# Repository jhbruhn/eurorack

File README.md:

# eurorack modules

Welcome to my Eurorack module stash. This is a collection of modules I (partially) designed for use with eurorack synthesizers.

## modules

* **bus**: A tiny bus. not much to say.
* **out**: Befaco Outs on a separate pcb with SMD parts to manufacture it via JLC
* **pure_adsr**: Alternative firmware for the old GMSN Pure ADSR modules, using ADSR and mini sequencer modes from Peaks and a weird looping ADSR thing on mode 3
* **stereo_mix**: a 4 channel stereo (input AND output) mixer with voltage-controlled panning and volume. Digitally controlled via Multiplying DACs (MCP4922 in combination with MCP4822)
* **vca**: A dual channel variable slope (exp/lin/log) VCA based on easily available components
* **vcf-20**: MS20 style filter
* **vcf-leiter**: Moog style filter

## license

Code: MIT license.

Hardware: cc-by-sa-3.0

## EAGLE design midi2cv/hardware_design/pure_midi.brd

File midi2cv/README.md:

# midi2cv
Eurorack Compatible, Arduino-based midi to cv converter with mono mode, arpeggiator and sequencer

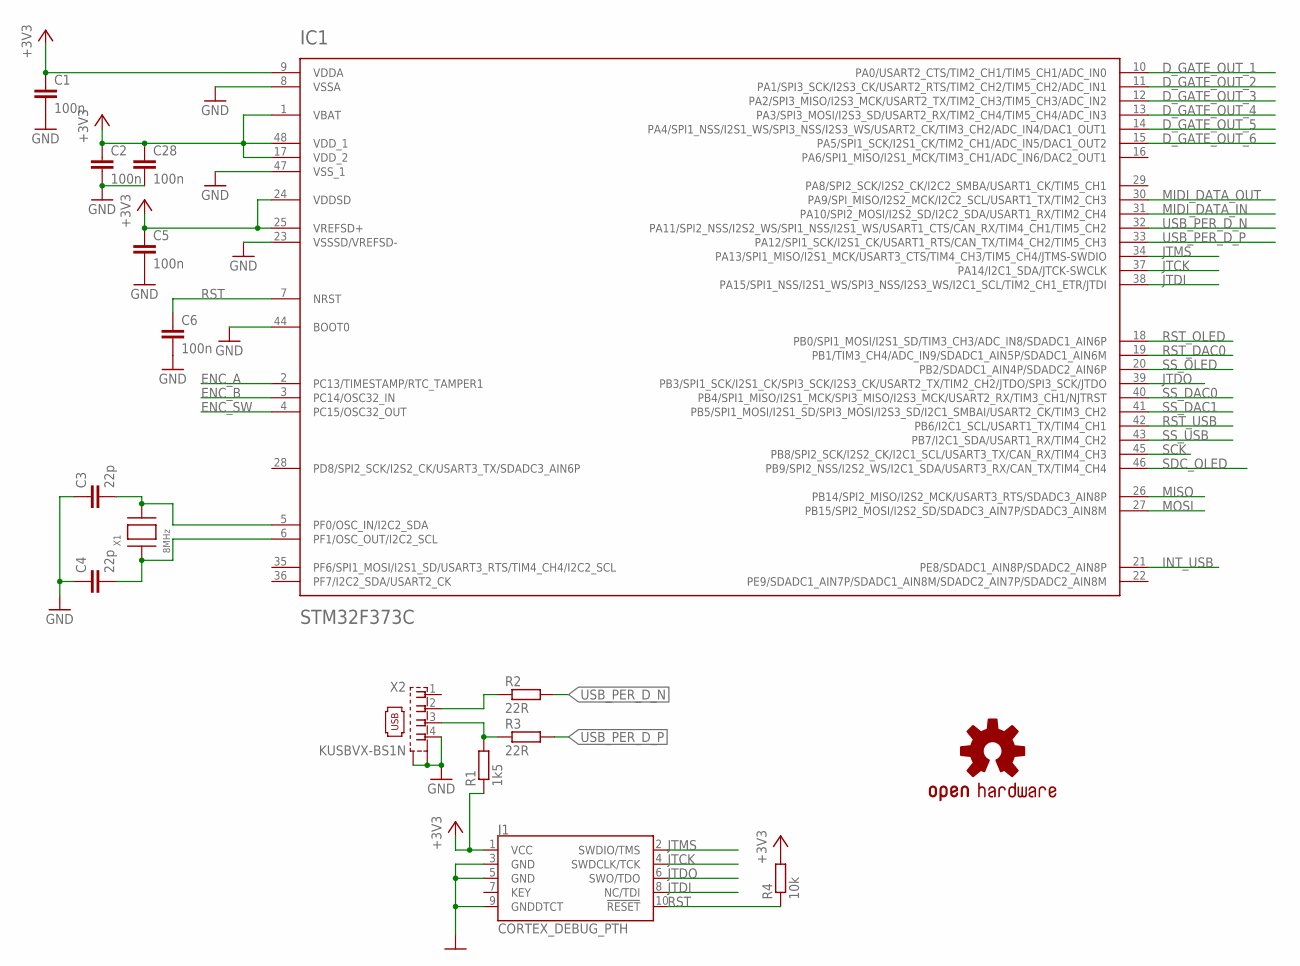
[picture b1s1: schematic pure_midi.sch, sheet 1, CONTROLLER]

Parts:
C1, C2, C5, C6, C28: 100n; C0603
C3, C4: 22p; C0603
IC1: STM32F373C; LQFP48
J1: CORTEX_DEBUG_PTH; 2X5-PTH-1.27MM
LOGO1: OSHW-LOGOM; OSHW-LOGO-M
R1: 1k5; R0603
R2, R3: 22R; R0603
R4: 10k; R0603
X1: 8MHz; NX5032
X2: KUSBVX-BS1N

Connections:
+3V3: C1.1, C2.1, C5.1, C28.1, IC1.1 (VBAT), IC1.9 (VDDA), IC1.17 (VDD_2), IC1.24 (VDDSD), IC1.25 (VREFSD+), IC1.48 (VDD_1), J1.1 (VCC), R1.1, R4.2; also elsewhere on the board
D_GATE_OUT_1: IC1.10 (PA0/USART2_CTS/TIM2_CH1/TIM5_CH1/ADC_IN0); also elsewhere on the board
D_GATE_OUT_2: IC1.11 (PA1/SPI3_SCK/I2S3_CK/USART2_RTS/TIM2_CH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); also elsewhere on the board
D_GATE_OUT_3: IC1.12 (PA2/SPI3_MISO/I2S3_MCK/USART2_TX/TIM2_C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); also elsewhere on the board
D_GATE_OUT_4: IC1.13 (PA3/SPI3_MOSI/I2S3_SD/USART2_RX/TIM2_CH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); also elsewhere on the board
D_GATE_OUT_5: IC1.14 (PA4/SPI1_NSS/I2S1_WS/SPI3_NSS/I2S3_WS/U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); also elsewhere on the board
D_GATE_OUT_6: IC1.15 (PA5/SPI1_SCK/I2S1_CK/TIM2_CH1/ADC_IN5/D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); also elsewhere on the board
ENC_A: IC1.2 (PC13/TIMESTAMP/RTC_TAMPER1); also elsewhere on the board
ENC_B: IC1.3 (PC14/OSC32_IN); also elsewhere on the board
ENC_SW: IC1.4 (PC15/OSC32_OUT); also elsewhere on the board
GND: C1.2, C2.2, C3.1, C4.1, C5.2, C6.2, C28.2, IC1.8 (VSSA), IC1.23 (VSSSD/VREFSD-), IC1.44 (BOOT0), IC1.47 (VSS_1), J1.3 (GND), J1.5 (GND), J1.9 (GNDDTCT), X2.4, X2.M1 (S1), X2.M2 (S2); also elsewhere on the board
INT_USB: IC1.21 (PE8/SDADC1_AIN8P/SDADC2_AIN8P)
JTCK: IC1.37 (PA14/I2C1_SDA/JTCK-SWCLK), J1.4 (SWDCLK/TCK)
JTDI: IC1.38 (PA15/SPI1_NSS/I2S1_WS/SPI3_NSS/I2S3_WS/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), J1.8 (NC/TDI)
JTDO: IC1.39 (PB3/SPI1_SCK/I2S1_CK/SPI3_SCK/I2S3_CK/U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), J1.6 (SWO/TDO)
JTMS: IC1.34 (PA13/SPI1_MISO/I2S1_MCK/USART3_CTS/TIM4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), J1.2 (SWDIO/TMS)
MIDI_DATA_IN: IC1.31 (PA10/SPI2_MOSI/I2S2_SD/I2C2_SDA/USART1_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); also elsewhere on the board
MIDI_DATA_OUT: IC1.30 (PA9/SPI_MISO/I2S2_MCK/I2C2_SCL/USART1_T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); also elsewhere on the board
MISO: IC1.26 (PB14/SPI2_MISO/I2S2_MCK/USART3_RTS/SDAD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)
MOSI: IC1.27 (PB15/SPI2_MOSI/I2S2_SD/SDADC3_AIN7P/SDA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); also elsewhere on the board
unnamed: C4.2, IC1.6 (PF1/OSC_OUT/I2C2_SCL), X1.P$1
unnamed: C3.2, IC1.5 (PF0/OSC_IN/I2C2_SDA), X1.P$2
unnamed: R2.1, X2.2
unnamed: R1.2, R3.1, X2.3
RST: C6.1, IC1.7 (NRST), J1.10 (!RESET), R4.1
RST_DAC0: IC1.19 (PB1/TIM3_CH4/ADC_IN9/SDADC1_AIN5P/SDADC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); also elsewhere on the board
RST_OLED: IC1.18 (PB0/SPI1_MOSI/I2S1_SD/TIM3_CH3/ADC_IN8/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); also elsewhere on the board
RST_USB: IC1.42 (PB6/I2C1_SCL/USART1_TX/TIM4_CH1)
SCK: IC1.45 (PB8/SPI2_SCK/I2S2_CK/I2C1_SCL/USART3_TX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); also elsewhere on the board
SDC_OLED: IC1.46 (PB9/SPI2_NSS/I2S2_WS/I2C1_SDA/USART3_RX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); also elsewhere on the board
SS_DAC0: IC1.40 (PB4/SPI1_MISO/I2S1_MCK/SPI3_MISO/I2S3_M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); also elsewhere on the board
SS_DAC1: IC1.41 (PB5/SPI1_MOSI/I2S1_SD/SPI3_MOSI/I2S3_SD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); also elsewhere on the board
SS_OLED: IC1.20 (PB2/SDADC1_AIN4P/SDADC2_AIN6P); also elsewhere on the board
SS_USB: IC1.43 (PB7/I2C1_SDA/USART1_RX/TIM4_CH2)
USB_PER_D_N: IC1.32 (PA11/SPI2_NSS/I2S2_WS/SPI1_NSS/I2S1_WS/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), R2.2
USB_PER_D_P: IC1.33 (PA12/SPI1_SCK/I2S1_CK/USART1_RTS/CAN_TX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), R3.2

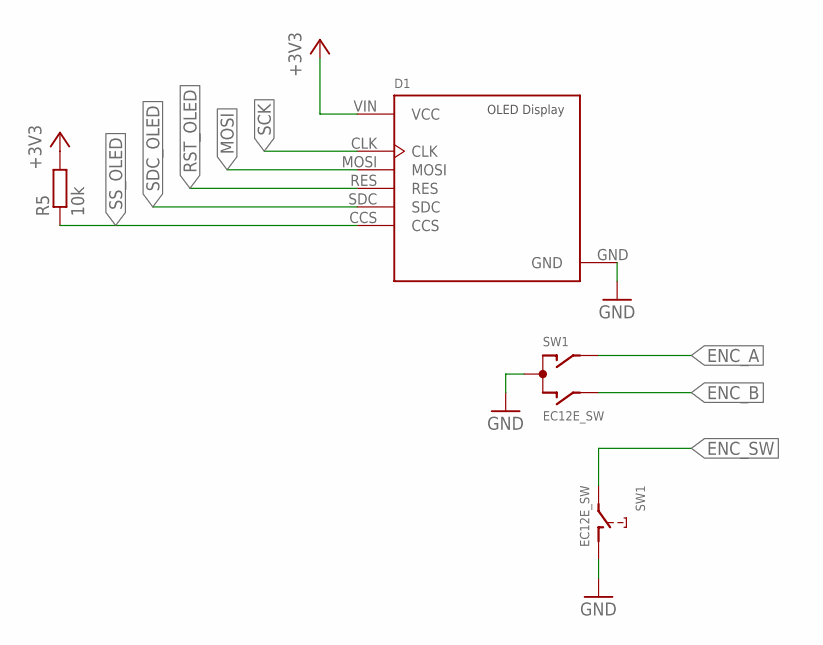
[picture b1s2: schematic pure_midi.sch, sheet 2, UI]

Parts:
D1: OLED_1.3_128X64_SPI; C1_ADAFRUIT_1.3_128X64_OLED
R5: 10k; R0603
SW1: EC12E_SW; ALPS_EC12E_SW

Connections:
+3V3: D1.VIN (VCC), R5.2; also elsewhere on the board
ENC_A: SW1.A; also elsewhere on the board
ENC_B: SW1.B; also elsewhere on the board
ENC_SW: SW1.E (2); also elsewhere on the board
GND: D1.GND, SW1.C, SW1.D (1); also elsewhere on the board
MOSI: D1.MOSI; also elsewhere on the board
RST_OLED: D1.RES; also elsewhere on the board
SCK: D1.CLK; also elsewhere on the board
SDC_OLED: D1.SDC; also elsewhere on the board
SS_OLED: D1.CCS, R5.1; also elsewhere on the board

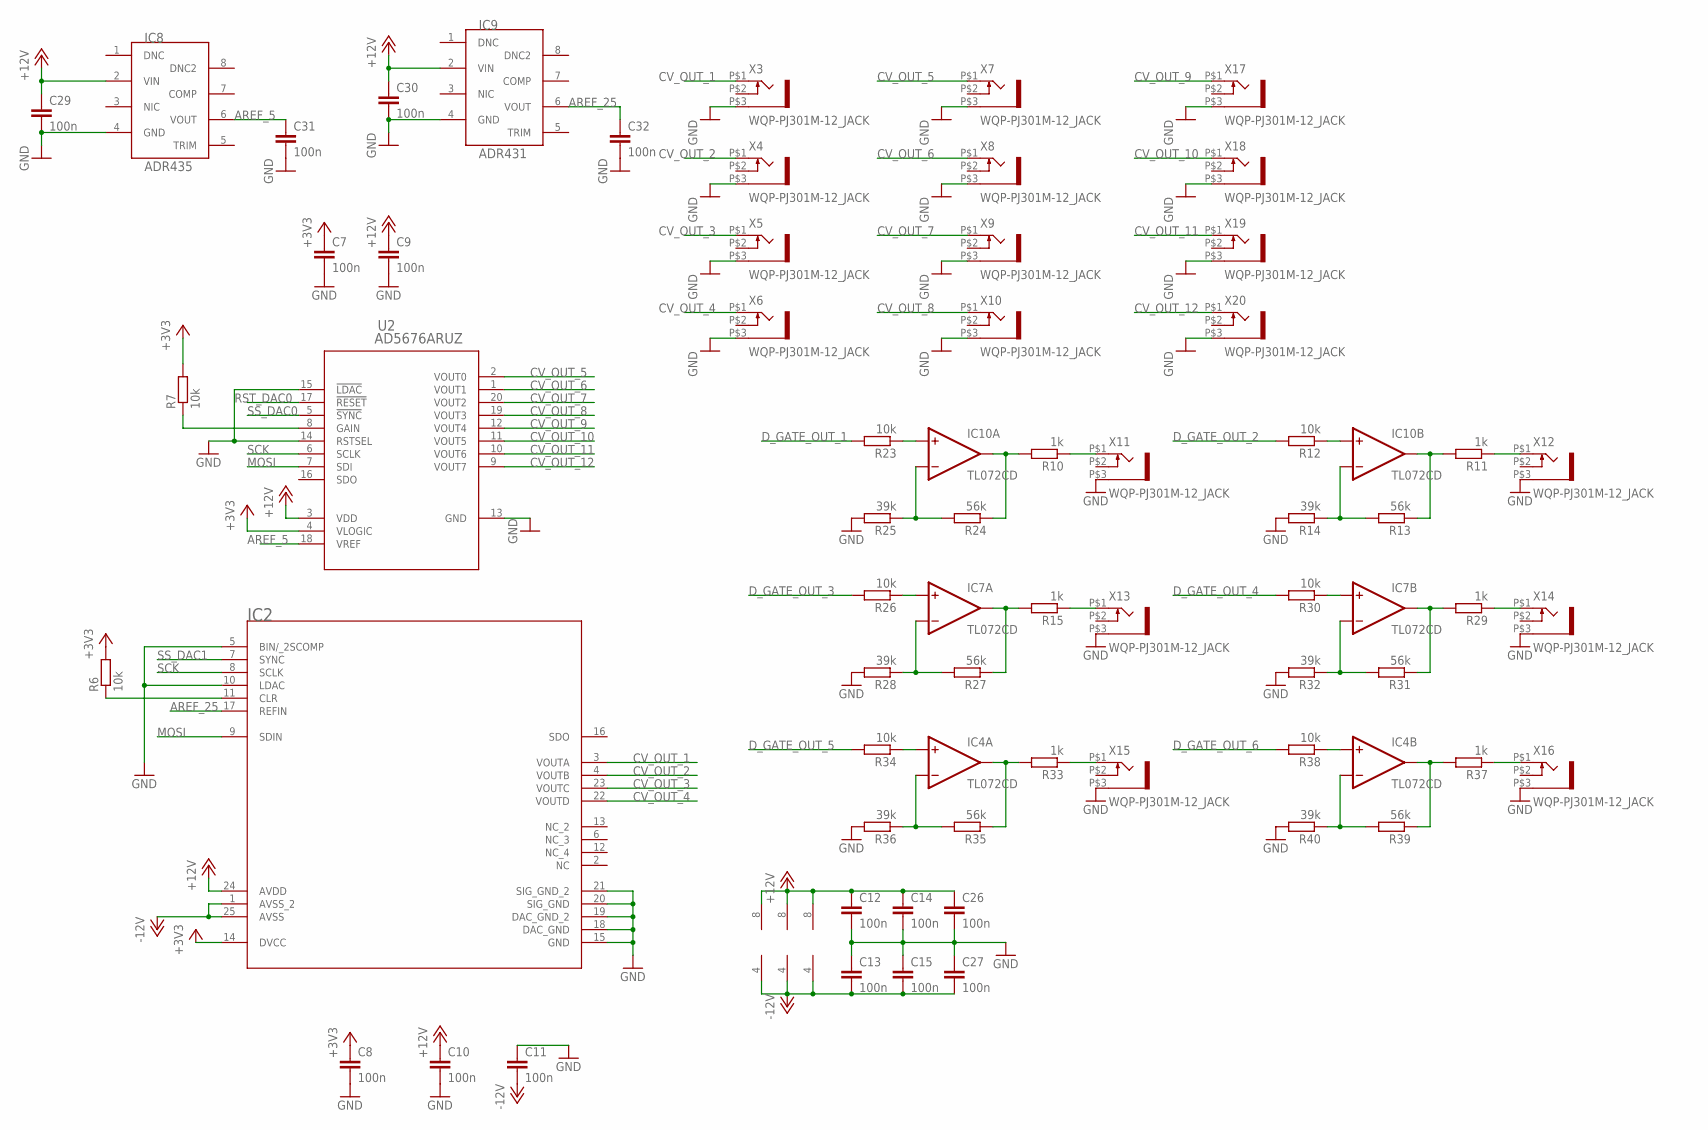
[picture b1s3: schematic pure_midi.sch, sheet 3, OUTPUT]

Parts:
C7, C8, C9, C10, C11, C12, C13, C14, C15, C26, C27, C29, C30, C31, C32: 100n; C0603
IC2: AD5754BREZ; RE_24
IC4, IC7, IC10: TL072CD; SOIC8
IC8: ADR435; MSOP8
IC9: ADR431; MSOP8
R6, R7, R12, R23, R26, R30, R34, R38: 10k; R0603
R10, R11, R15, R29, R33, R37: 1k; R0603
R13, R24, R27, R31, R35, R39: 56k; R0603
R14, R25, R28, R32, R36, R40: 39k; R0603
U2: AD5676ARUZ; RU_20
X3, X4, X5, X6, X7, X8, X9, X10, X11, X12, X13, X14, X15, X16, X17, X18, X19, X20: WQP-PJ301M-12_JACK

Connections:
+3V3: C7.1, C8.1, IC2.14 (DVCC), R6.2, R7.2, U2.4 (VLOGIC); also elsewhere on the board
+12V: C9.1, C10.1, C12.1, C14.1, C26.1, C29.1, C30.1, IC2.24 (AVDD), IC4.8 (V+), IC7.8 (V+), IC8.2 (VIN), IC9.2 (VIN), IC10.8 (V+), U2.3 (VDD); also elsewhere on the board
-12V: C11.2, C13.2, C15.2, C27.2, IC2.1 (AVSS_2), IC2.25 (AVSS), IC4.4 (V-), IC7.4 (V-), IC10.4 (V-); also elsewhere on the board
AREF_5: C31.1, IC8.6 (VOUT), U2.18 (VREF)
AREF_25: C32.1, IC2.17 (REFIN), IC9.6 (VOUT)
CV_OUT_1: IC2.3 (VOUTA), X3.P$1 (2)
CV_OUT_2: IC2.4 (VOUTB), X4.P$1 (2)
CV_OUT_3: IC2.23 (VOUTC), X5.P$1 (2)
CV_OUT_4: IC2.22 (VOUTD), X6.P$1 (2)
CV_OUT_5: U2.2 (VOUT0), X7.P$1 (2)
CV_OUT_6: U2.1 (VOUT1), X8.P$1 (2)
CV_OUT_7: U2.20 (VOUT2), X9.P$1 (2)
CV_OUT_8: U2.19 (VOUT3), X10.P$1 (2)
CV_OUT_9: U2.12 (VOUT4), X17.P$1 (2)
CV_OUT_10: U2.11 (VOUT5), X18.P$1 (2)
CV_OUT_11: U2.10 (VOUT6), X19.P$1 (2)
CV_OUT_12: U2.9 (VOUT7), X20.P$1 (2)
D_GATE_OUT_1: R23.2; also elsewhere on the board
D_GATE_OUT_2: R12.2; also elsewhere on the board
D_GATE_OUT_3: R26.2; also elsewhere on the board
D_GATE_OUT_4: R30.2; also elsewhere on the board
D_GATE_OUT_5: R34.2; also elsewhere on the board
D_GATE_OUT_6: R38.2; also elsewhere on the board
GATE_OUT_1: R10.1, X11.P$1 (2)
GATE_OUT_2: R11.1, X12.P$1 (2)
GATE_OUT_3: R15.1, X13.P$1 (2)
GATE_OUT_4: R29.1, X14.P$1 (2)
GATE_OUT_6: R37.1, X16.P$1 (2)
GND: C7.2, C8.2, C9.2, C10.2, C11.1, C12.2, C13.1, C14.2, C15.1, C26.2, C27.1, C29.2, C30.2, C31.2, C32.2, IC2.5 (BIN/_2SCOMP), IC2.10 (LDAC), IC2.15 (GND), IC2.18 (DAC_GND), IC2.19 (DAC_GND_2), IC2.20 (SIG_GND), IC2.21 (SIG_GND_2), IC8.4 (GND), IC9.4 (GND), R14.2, R25.2, R28.2, R32.2, R36.2, R40.2, U2.13 (GND), U2.14 (RSTSEL), U2.15 (!LDAC), X3.P$3 (1), X4.P$3 (1), X5.P$3 (1), X6.P$3 (1), X7.P$3 (1), X8.P$3 (1), X9.P$3 (1), X10.P$3 (1), X11.P$3 (1), X12.P$3 (1), X13.P$3 (1), X14.P$3 (1), X15.P$3 (1), X16.P$3 (1), X17.P$3 (1), X18.P$3 (1), X19.P$3 (1), X20.P$3 (1); also elsewhere on the board
MOSI: IC2.9 (SDIN), U2.7 (SDI); also elsewhere on the board
unnamed: R7.1, U2.8 (GAIN)
unnamed: IC2.11 (CLR), R6.1
unnamed: IC10.1 (OUT), R10.2, R24.1
unnamed: IC10.7 (OUT), R11.2, R13.1
unnamed: IC10.6 (-IN), R13.2, R14.1
unnamed: IC10.5 (+IN), R12.1
unnamed: IC10.2 (-IN), R24.2, R25.1
unnamed: IC7.1 (OUT), R15.2, R27.1
unnamed: IC7.2 (-IN), R27.2, R28.1
unnamed: IC7.3 (+IN), R26.1
unnamed: IC10.3 (+IN), R23.1
unnamed: IC7.7 (OUT), R29.2, R31.1
unnamed: IC7.6 (-IN), R31.2, R32.1
unnamed: IC7.5 (+IN), R30.1
unnamed: IC4.1 (OUT), R33.2, R35.1
unnamed: IC4.2 (-IN), R35.2, R36.1
unnamed: IC4.3 (+IN), R34.1
unnamed: IC4.7 (OUT), R37.2, R39.1
unnamed: IC4.6 (-IN), R39.2, R40.1
unnamed: IC4.5 (+IN), R38.1
unnamed: R33.1, X15.P$1 (2)
RST_DAC0: U2.17 (!RESET); also elsewhere on the board
SCK: IC2.8 (SCLK), U2.6 (SCLK); also elsewhere on the board
SS_DAC0: U2.5 (!SYNC); also elsewhere on the board
SS_DAC1: IC2.7 (SYNC); also elsewhere on the board

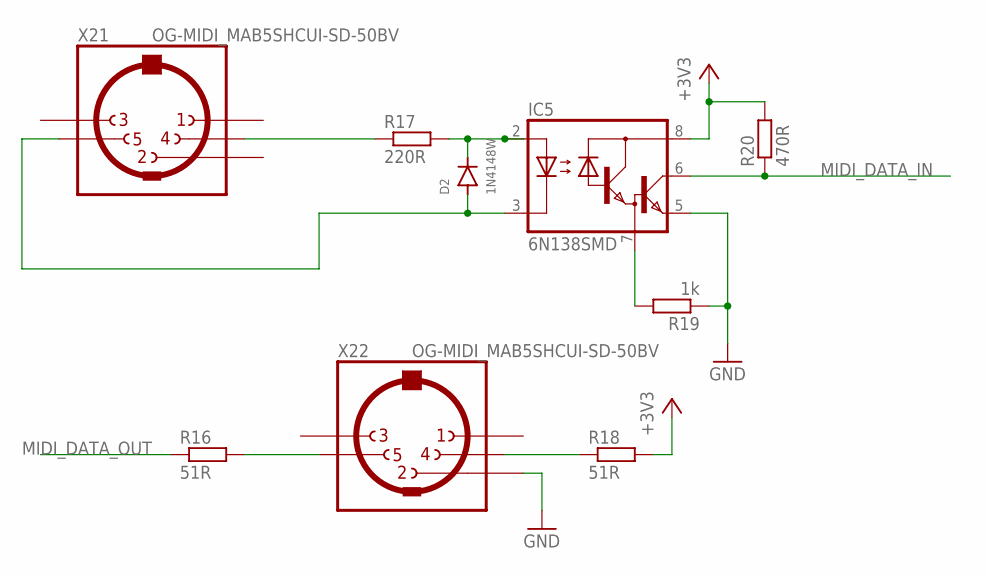
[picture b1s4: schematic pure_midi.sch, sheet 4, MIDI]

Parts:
D2: 1N4148W; SOD123
IC5: 6N138SMD; SO8-GW300
R16, R18: 51R; R0603
R17: 220R; R0603
R19: 1k; R0603
R20: 470R; R0603
X21, X22: OG-MIDI_MAB5SHCUI-SD-50BV; OG-MIDI_SD-50BV

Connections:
+3V3: IC5.8 (VCC), R18.2, R20.2; also elsewhere on the board
GND: IC5.5 (GND), R19.1, X22.2; also elsewhere on the board
MIDI_DATA_IN: IC5.6 (VO), R20.1; also elsewhere on the board
MIDI_DATA_OUT: R16.1; also elsewhere on the board
unnamed: D2.C, IC5.2 (A), R17.2
unnamed: R17.1, X21.4
unnamed: D2.A, IC5.3 (C), X21.5
unnamed: IC5.7 (VB), R19.2
unnamed: R16.2, X22.5
unnamed: R18.1, X22.4

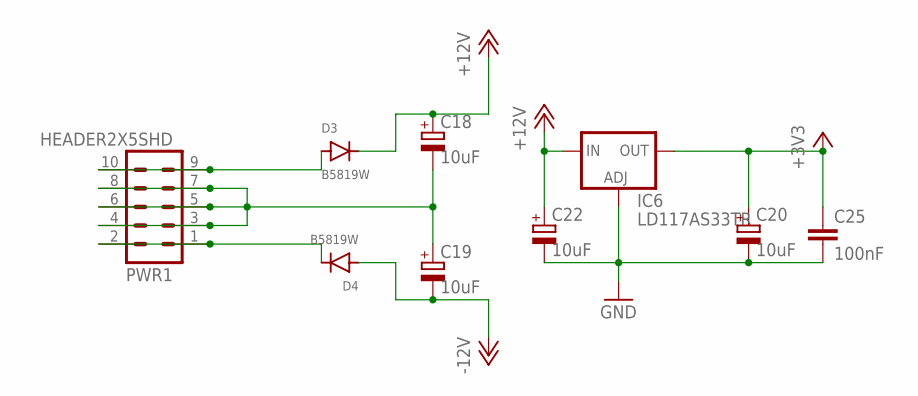
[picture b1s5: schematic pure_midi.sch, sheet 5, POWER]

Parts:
C18, C19, C20, C22: 10uF; CASE-A_3216
C25: 100nF; C0603
D3, D4: B5819W; SOD123
IC6: LD117AS33TR; SOT223
PWR1: HEADER2X5SHD; 2X5-SHROUDED

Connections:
+3V3: C20.+, C25.1, IC6.4 (OUT); also elsewhere on the board
+12V: C18.+, C22.+, D3.C, IC6.3 (IN); also elsewhere on the board
-12V: C19.-, D4.A; also elsewhere on the board
GND: C20.-, C22.-, C25.2, IC6.1 (ADJ); also elsewhere on the board
unnamed: C18.-, C19.+, PWR1.3, PWR1.4, PWR1.5, PWR1.6, PWR1.7, PWR1.8
unnamed: D3.A, PWR1.9, PWR1.10
unnamed: D4.C, PWR1.1, PWR1.2

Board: 2 copper layers, 103 parts (75 on the bottom side), 83 nets, no tracks yet.

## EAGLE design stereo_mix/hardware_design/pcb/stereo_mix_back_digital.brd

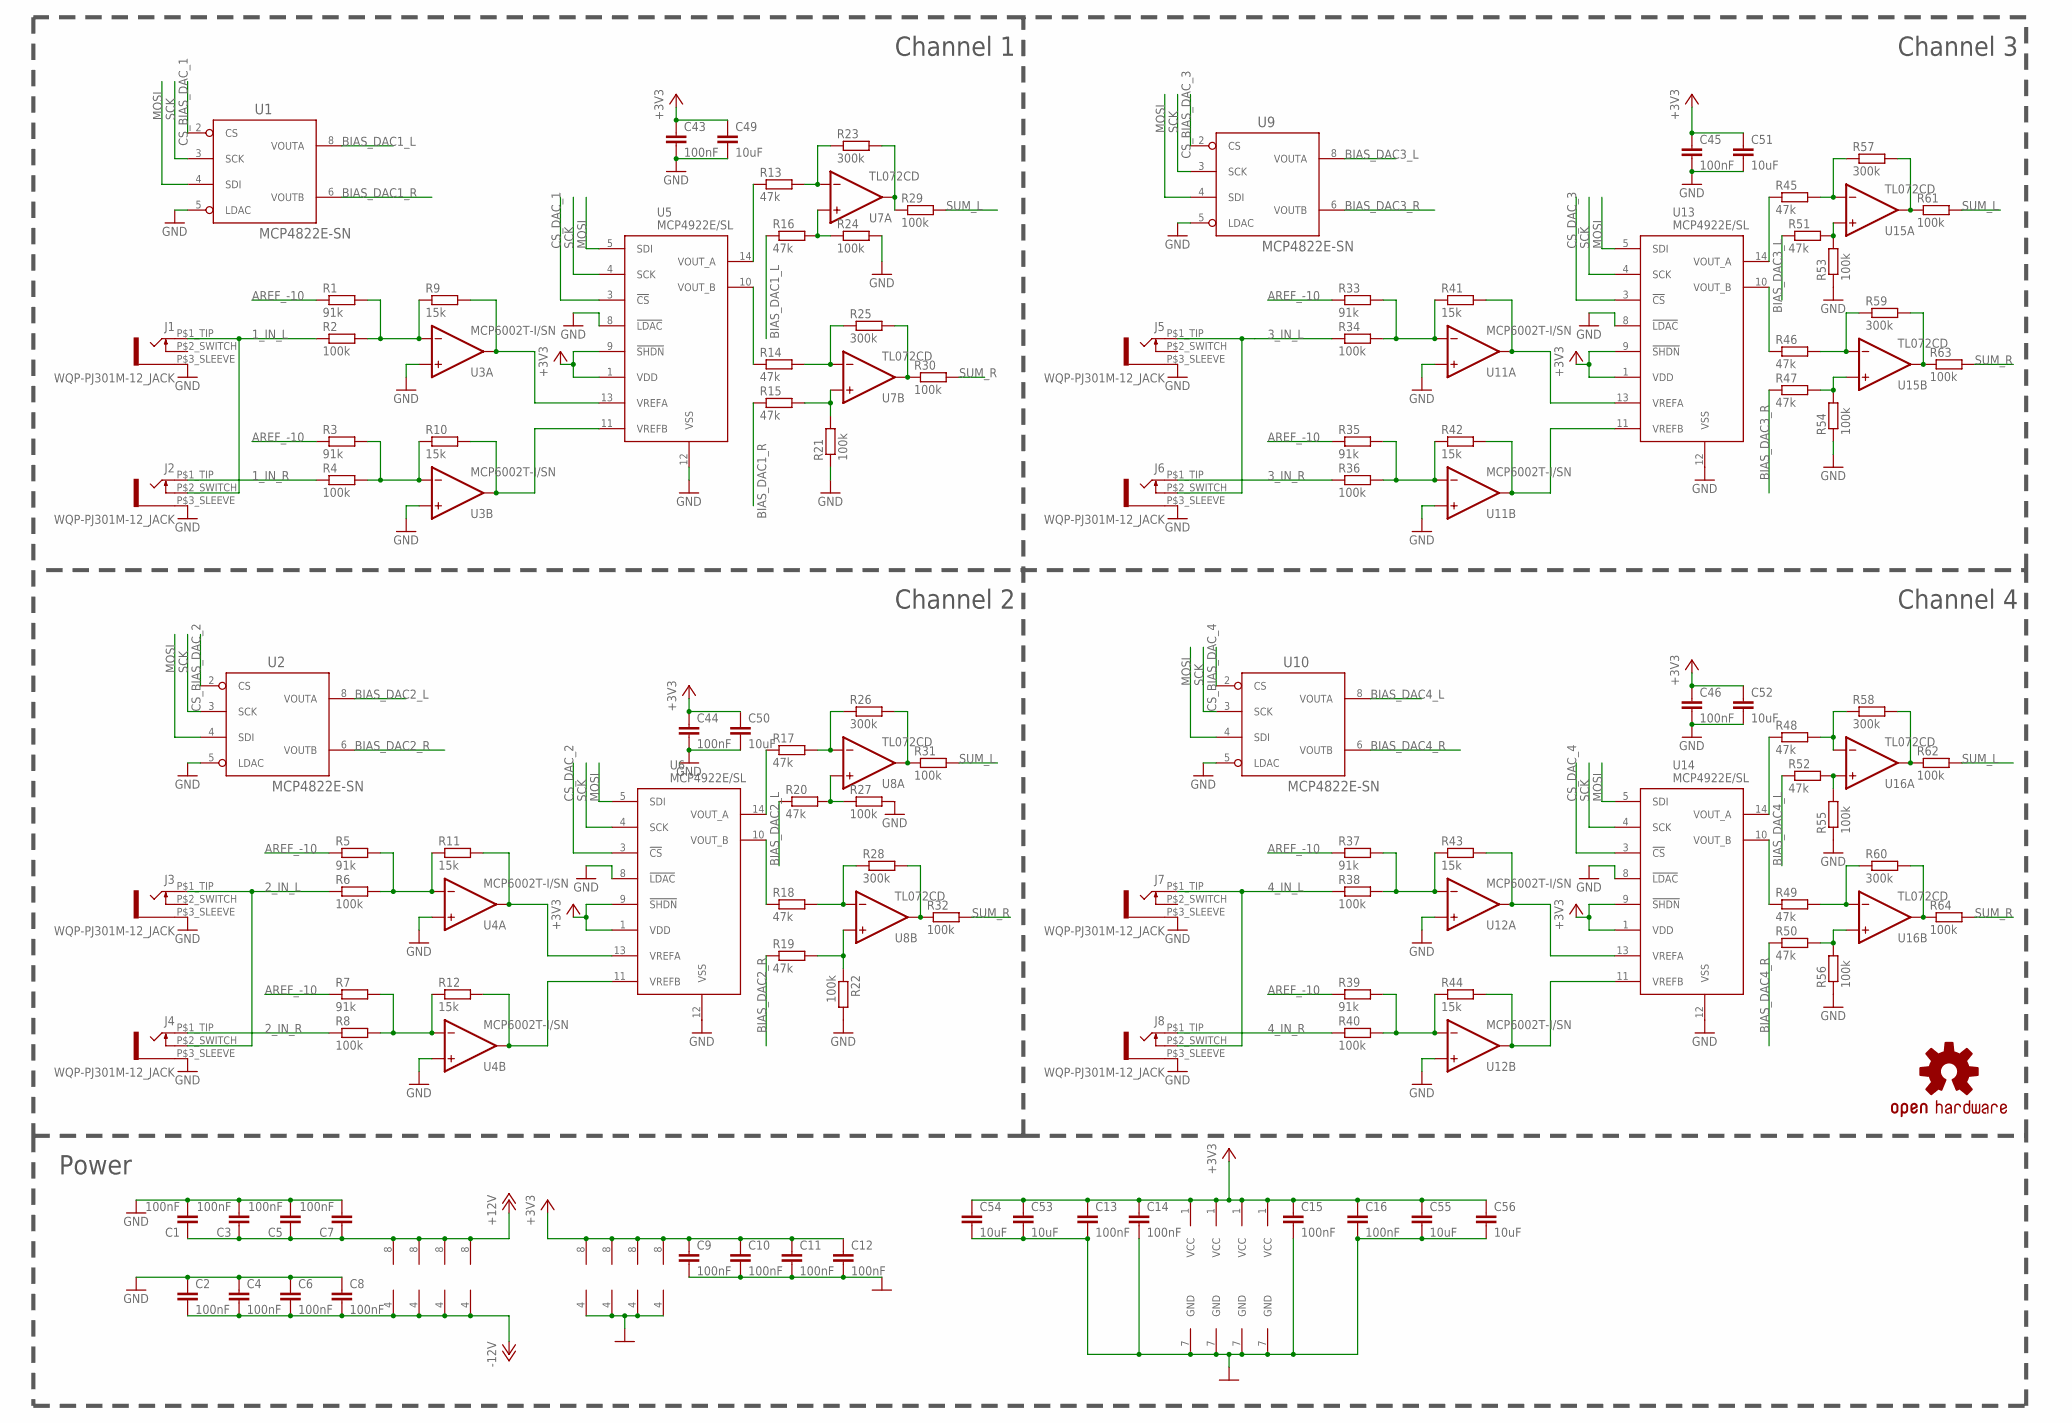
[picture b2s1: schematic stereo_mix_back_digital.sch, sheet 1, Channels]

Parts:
C1, C2, C3, C4, C5, C6, C7, C8, C9, C10, C11, C12, C13, C14, C15, C16, C43, C44, C45, C46: 100nF; C0402
C49, C50, C51, C52, C53, C54, C55, C56: 10uF; C0805
J1, J2, J3, J4, J5, J6, J7, J8: WQP-PJ301M-12_JACK
LOGO1: OSHW-LOGOS; OSHW-LOGO-S
R1, R3, R5, R7, R33, R35, R37, R39: 91k; R0402
R2, R4, R6, R8, R21, R22, R24, R27, R29, R30, R31, R32, R34, R36, R38, R40, R53, R54, R55, R56, R61, R62, R63, R64: 100k; R0402
R9, R10, R11, R12, R41, R42, R43, R44: 15k; R0402
R13, R14, R15, R16, R17, R18, R19, R20, R45, R46, R47, R48, R49, R50, R51, R52: 47k; R0402
R23, R25, R26, R28, R57, R58, R59, R60: 300k; R0402
U1, U2, U9, U10: MCP4822E-SN; SOIC8
U3, U4, U11, U12: MCP6002T-I/SN; SOIC8
U5, U6, U13, U14: MCP4922E/SL; SO-14
U7, U8, U15, U16: TL072CD; SOIC8

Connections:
1_IN_L: J1.P$1_TIP (2), J2.P$2_SWITCH (3), R2.1
1_IN_R: J2.P$1_TIP (2), R4.1
2_IN_L: J3.P$1_TIP (2), J4.P$2_SWITCH (3), R6.1
2_IN_R: J4.P$1_TIP (2), R8.1
3_IN_L: J5.P$1_TIP (2), J6.P$2_SWITCH (3), R34.1
3_IN_R: J6.P$1_TIP (2), R36.1
4_IN_L: J7.P$1_TIP (2), J8.P$2_SWITCH (3), R38.1
4_IN_R: J8.P$1_TIP (2), R40.1
+3V3: C9.1, C10.1, C11.1, C12.1, C13.1, C14.1, C15.1, C16.1, C43.1, C44.1, C45.1, C46.1, C49.1, C50.1, C51.1, C52.1, C53.1, C54.1, C55.1, C56.1, U1.1 (VCC), U2.1 (VCC), U3.8 (V+), U4.8 (V+), U5.1 (VDD), U5.9 (!SHDN), U6.1 (VDD), U6.9 (!SHDN), U9.1 (VCC), U10.1 (VCC), U11.8 (V+), U12.8 (V+), U13.1 (VDD), U13.9 (!SHDN), U14.1 (VDD), U14.9 (!SHDN); also elsewhere on the board
+12V: C1.1, C3.1, C5.1, C7.1, U7.8 (V+), U8.8 (V+), U15.8 (V+), U16.8 (V+); also elsewhere on the board
-12V: C2.2, C4.2, C6.2, C8.2, U7.4 (V-), U8.4 (V-), U15.4 (V-), U16.4 (V-); also elsewhere on the board
AREF_-10: R1.1, R3.1, R5.1, R7.1, R33.1, R35.1, R37.1, R39.1; also elsewhere on the board
BIAS_DAC1_L: R16.1, U1.8 (VOUTA)
BIAS_DAC1_R: R15.1, U1.6 (VOUTB)
BIAS_DAC2_L: R20.1, U2.8 (VOUTA)
BIAS_DAC2_R: R19.1, U2.6 (VOUTB)
BIAS_DAC3_L: R51.1, U9.8 (VOUTA)
BIAS_DAC3_R: R47.1, U9.6 (VOUTB)
BIAS_DAC4_L: R52.1, U10.8 (VOUTA)
BIAS_DAC4_R: R50.1, U10.6 (VOUTB)
CS_BIAS_DAC_1: U1.2 (CS); also elsewhere on the board
CS_BIAS_DAC_2: U2.2 (CS); also elsewhere on the board
CS_BIAS_DAC_3: U9.2 (CS); also elsewhere on the board
CS_BIAS_DAC_4: U10.2 (CS); also elsewhere on the board
CS_DAC_1: U5.3 (!CS); also elsewhere on the board
CS_DAC_2: U6.3 (!CS); also elsewhere on the board
CS_DAC_3: U13.3 (!CS); also elsewhere on the board
CS_DAC_4: U14.3 (!CS); also elsewhere on the board
GND: C1.2, C2.1, C3.2, C4.1, C5.2, C6.1, C7.2, C8.1, C9.2, C10.2, C11.2, C12.2, C13.2, C14.2, C15.2, C16.2, C43.2, C44.2, C45.2, C46.2, C49.2, C50.2, C51.2, C52.2, C53.2, C54.2, C55.2, C56.2, J1.P$3_SLEEVE (1), J2.P$3_SLEEVE (1), J3.P$3_SLEEVE (1), J4.P$3_SLEEVE (1), J5.P$3_SLEEVE (1), J6.P$3_SLEEVE (1), J7.P$3_SLEEVE (1), J8.P$3_SLEEVE (1), R21.1, R22.2, R24.2, R27.2, R53.1, R54.1, R55.1, R56.1, U1.5 (LDAC), U1.7 (GND), U2.5 (LDAC), U2.7 (GND), U3.3 (+IN), U3.4 (V-), U3.5 (+IN), U4.3 (+IN), U4.4 (V-), U4.5 (+IN), U5.8 (!LDAC), U5.12 (VSS), U6.8 (!LDAC), U6.12 (VSS), U9.5 (LDAC), U9.7 (GND), U10.5 (LDAC), U10.7 (GND), U11.3 (+IN), U11.4 (V-), U11.5 (+IN), U12.3 (+IN), U12.4 (V-), U12.5 (+IN), U13.8 (!LDAC), U13.12 (VSS), U14.8 (!LDAC), U14.12 (VSS); also elsewhere on the board
MOSI: U1.4 (SDI), U2.4 (SDI), U5.5 (SDI), U6.5 (SDI), U9.4 (SDI), U10.4 (SDI), U13.5 (SDI), U14.5 (SDI); also elsewhere on the board
unnamed: R13.1, U5.14 (VOUT_A)
unnamed: R3.2, R4.2, R10.1, U3.6 (-IN)
unnamed: R13.2, R23.1, U7.2 (-IN)
unnamed: R9.2, U3.1 (OUT), U5.13 (VREFA)
unnamed: R10.2, U3.7 (OUT), U5.11 (VREFB)
unnamed: R1.2, R2.2, R9.1, U3.2 (-IN)
unnamed: R25.2, R30.1, U7.7 (OUT)
unnamed: R23.2, R29.1, U7.1 (OUT)
unnamed: R14.2, R25.1, U7.6 (-IN)
unnamed: R14.1, U5.10 (VOUT_B)
unnamed: R16.2, R24.1, U7.3 (+IN)
unnamed: R15.2, R21.2, U7.5 (+IN)
unnamed: R7.2, R8.2, R12.1, U4.6 (-IN)
unnamed: R12.2, U4.7 (OUT), U6.11 (VREFB)
unnamed: R11.2, U4.1 (OUT), U6.13 (VREFA)
unnamed: R5.2, R6.2, R11.1, U4.2 (-IN)
unnamed: R17.1, U6.14 (VOUT_A)
unnamed: R17.2, R26.1, U8.2 (-IN)
unnamed: R26.2, R31.1, U8.1 (OUT)
unnamed: R18.2, R28.1, U8.6 (-IN)
unnamed: R18.1, U6.10 (VOUT_B)
unnamed: R28.2, R32.1, U8.7 (OUT)
unnamed: R35.2, R36.2, R42.1, U11.6 (-IN)
unnamed: R42.2, U11.7 (OUT), U13.11 (VREFB)
unnamed: R41.2, U11.1 (OUT), U13.13 (VREFA)
unnamed: R33.2, R34.2, R41.1, U11.2 (-IN)
unnamed: R45.1, U13.14 (VOUT_A)
unnamed: R45.2, R57.1, U15.2 (-IN)
unnamed: R57.2, R61.1, U15.1 (OUT)
unnamed: R46.2, R59.1, U15.6 (-IN)
unnamed: R46.1, U13.10 (VOUT_B)
unnamed: R59.2, R63.1, U15.7 (OUT)
unnamed: R39.2, R40.2, R44.1, U12.6 (-IN)
unnamed: R44.2, U12.7 (OUT), U14.11 (VREFB)
unnamed: R43.2, U12.1 (OUT), U14.13 (VREFA)
unnamed: R37.2, R38.2, R43.1, U12.2 (-IN)
unnamed: R48.1, U14.14 (VOUT_A)
unnamed: R48.2, R58.1, U16.2 (-IN)
unnamed: R58.2, R62.1, U16.1 (OUT)
unnamed: R49.2, R60.1, U16.6 (-IN)
unnamed: R49.1, U14.10 (VOUT_B)
unnamed: R60.2, R64.1, U16.7 (OUT)
unnamed: R20.2, R27.1, U8.3 (+IN)
unnamed: R19.2, R22.1, U8.5 (+IN)
unnamed: R51.2, R53.2, U15.3 (+IN)
unnamed: R47.2, R54.2, U15.5 (+IN)
unnamed: R50.2, R56.2, U16.5 (+IN)
unnamed: R52.2, R55.2, U16.3 (+IN)
SCK: U1.3 (SCK), U2.3 (SCK), U5.4 (SCK), U6.4 (SCK), U9.3 (SCK), U10.3 (SCK), U13.4 (SCK), U14.4 (SCK); also elsewhere on the board
SUM_L: R29.2, R31.2, R61.2, R62.2; also elsewhere on the board
SUM_R: R30.2, R32.2, R63.2, R64.2; also elsewhere on the board

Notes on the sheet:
Channel 1
Channel 2
Channel 3
Channel 4
Power

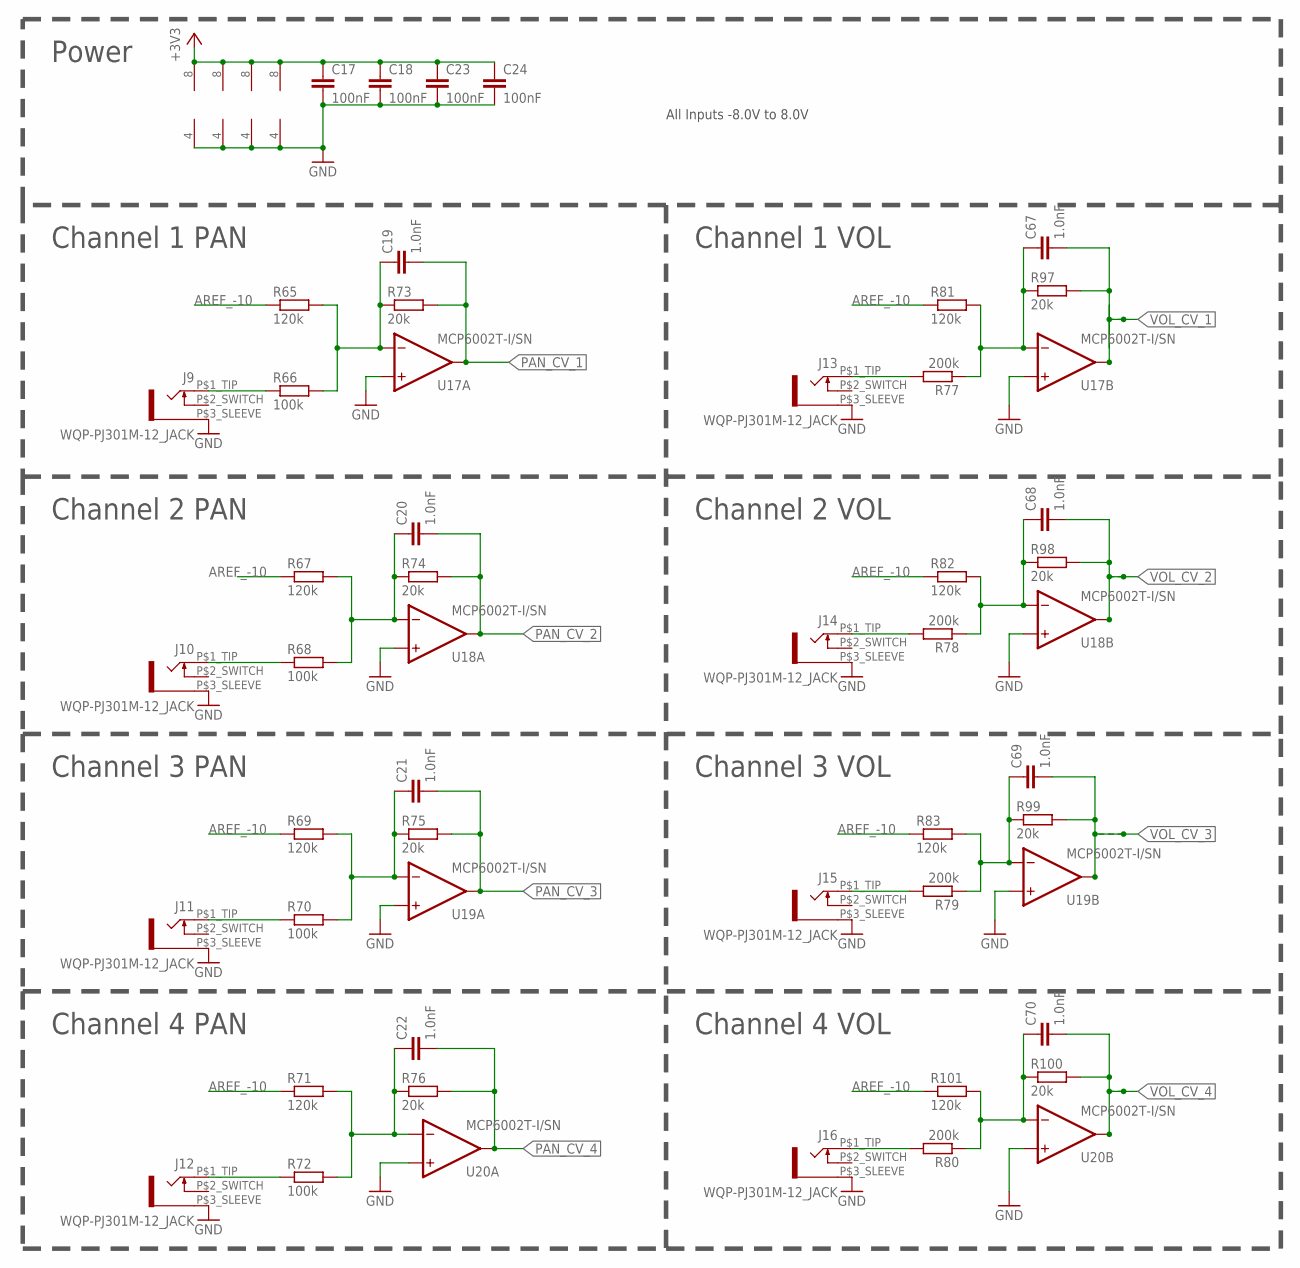
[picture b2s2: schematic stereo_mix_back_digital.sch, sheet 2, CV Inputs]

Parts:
C17, C18, C23, C24: 100nF; C0402
C19, C20, C21, C22, C67, C68, C69, C70: 1.0nF; C0402
J9, J10, J11, J12, J13, J14, J15, J16: WQP-PJ301M-12_JACK
R65, R67, R69, R71, R81, R82, R83, R101: 120k; R0402
R66, R68, R70, R72: 100k; R0402
R73, R74, R75, R76, R97, R98, R99, R100: 20k; R0402
R77, R78, R79, R80: 200k; R0402
U17, U18, U19, U20: MCP6002T-I/SN; SOIC8

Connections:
2_PAN_CV_IN: J10.P$1_TIP (2), R68.1
2_VOLUME_CV: J14.P$1_TIP (2), R78.2
3_PAN_CV_IN: J11.P$1_TIP (2), R70.1
3_VOLUME_CV: J15.P$1_TIP (2), R79.2
4_PAN_CV_IN: J12.P$1_TIP (2), R72.1
4_VOLUME_CV: J16.P$1_TIP (2), R80.2
+3V3: C17.1, C18.1, C23.1, C24.1, U17.8 (V+), U18.8 (V+), U19.8 (V+), U20.8 (V+); also elsewhere on the board
AREF_-10: R65.1, R67.1, R69.1, R71.1, R81.1, R82.1, R83.1, R101.1; also elsewhere on the board
GND: C17.2, C18.2, C23.2, C24.2, J9.P$3_SLEEVE (1), J10.P$3_SLEEVE (1), J11.P$3_SLEEVE (1), J12.P$3_SLEEVE (1), J13.P$3_SLEEVE (1), J14.P$3_SLEEVE (1), J15.P$3_SLEEVE (1), J16.P$3_SLEEVE (1), U17.3 (+IN), U17.4 (V-), U17.5 (+IN), U18.3 (+IN), U18.4 (V-), U18.5 (+IN), U19.3 (+IN), U19.4 (V-), U19.5 (+IN), U20.3 (+IN), U20.4 (V-), U20.5 (+IN); also elsewhere on the board
unnamed: C69.1, R79.1, R83.2, R99.1, U19.6 (-IN)
unnamed: C70.1, R80.1, R100.1, R101.2, U20.6 (-IN)
unnamed: C19.1, R65.2, R66.2, R73.1, U17.2 (-IN)
unnamed: C22.1, R71.2, R72.2, R76.1, U20.2 (-IN)
unnamed: C21.1, R69.2, R70.2, R75.1, U19.2 (-IN)
unnamed: C20.1, R67.2, R68.2, R74.1, U18.2 (-IN)
unnamed: C67.1, R77.1, R81.2, R97.1, U17.6 (-IN)
unnamed: C68.1, R78.1, R82.2, R98.1, U18.6 (-IN)
unnamed: J9.P$1_TIP (2), R66.1
unnamed: J13.P$1_TIP (2), R77.2
PAN_CV_1: C19.2, R73.2, U17.1 (OUT); also elsewhere on the board
PAN_CV_2: C20.2, R74.2, U18.1 (OUT); also elsewhere on the board
PAN_CV_3: C21.2, R75.2, U19.1 (OUT); also elsewhere on the board
PAN_CV_4: C22.2, R76.2, U20.1 (OUT); also elsewhere on the board
VOL_CV_1: C67.2, R97.2, U17.7 (OUT); also elsewhere on the board
VOL_CV_2: C68.2, R98.2, U18.7 (OUT); also elsewhere on the board
VOL_CV_3: C69.2, R99.2, U19.7 (OUT); also elsewhere on the board
VOL_CV_4: C70.2, R100.2, U20.7 (OUT); also elsewhere on the board

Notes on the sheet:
Power
Channel 1 PAN
Channel 1 VOL
Channel 2 VOL
Channel 3 VOL
Channel 4 VOL
Channel 4 PAN
Channel 3 PAN
Channel 2 PAN
All Inputs -8.0V to 8.0V

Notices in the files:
parts and their libraries:
SparkFun-IC-Microcontroller: Licensing: Creative Commons ShareAlike 4.0 International - https://creativecommons.org/licenses/by-sa/4.0
op-amp: Copyright (C) 2006 by Bob Starr
